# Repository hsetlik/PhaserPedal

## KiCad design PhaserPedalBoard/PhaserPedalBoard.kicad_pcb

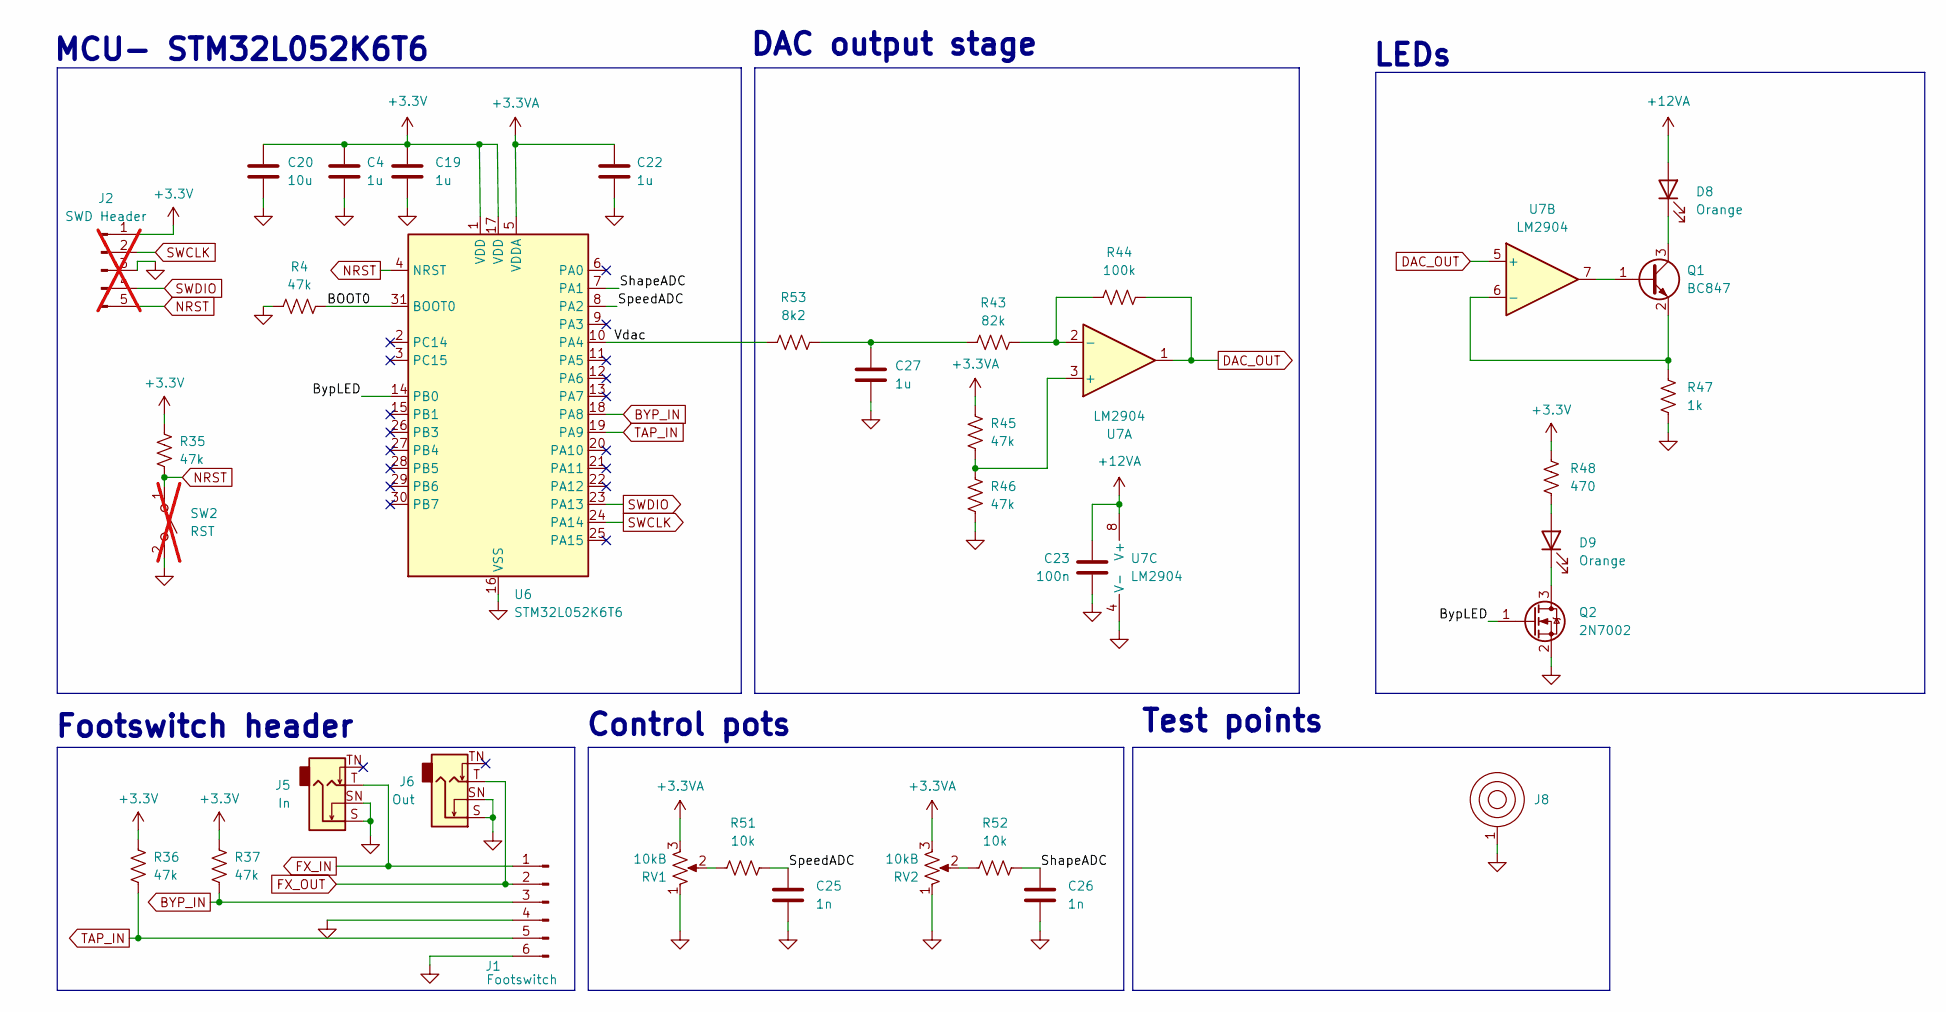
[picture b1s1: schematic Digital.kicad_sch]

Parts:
C4, C19, C22, C27: 1u; C_0805_2012Metric
C20: 10u; C_0805_2012Metric
C23: 100n; C_0805_2012Metric
C25, C26: 1n; C_0805_2012Metric
D8, D9: Orange; LED_D3.0mm; MPN LTL-4291N
J1: Footswitch; PinHeader_1x06_P2.54mm_Vertical
J2: SWD Header; PinHeader_1x05_P2.54mm_Vertical; not fitted
J5: In; Jack_6.35mm_Tayda_PJ664C_Mono_Horizontal; MPN PJ-644C MONO
J6: Out; Jack_6.35mm_Tayda_PJ664C_Mono_Horizontal; MPN PJ-644C MONO
J8: BatteryContact_Keystone_243
Q1: BC847; SOT-23
Q2: 2N7002; SOT-23; MPN 2N7002NXAKR
R4, R45, R46: 47k; R_0805_2012Metric
R35, R36, R37: 47k; R_0805_2012Metric; MPN RK73B2ATTE473J
R43: 82k; R_0805_2012Metric
R44: 100k; R_0805_2012Metric
R47: 1k; R_0805_2012Metric
R48: 470; R_0805_2012Metric; MPN RC0805JR-10470RL
R51, R52: 10k; R_0805_2012Metric
R53: 8k2; R_0805_2012Metric
RV1, RV2: 10kB; Potentiometer_Alpha_RV16AF_42_Single_Long; MPN RV9022NO-PA30B7.0-B10K-000-W3.0
SW2: RST; SW_SPST_B3U-1000P; not fitted
U6: STM32L052K6T6; LQFP-32_7x7mm_P0.8mm
U7: LM2904; SOIC-8_3.9x4.9mm_P1.27mm

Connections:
+3.3V: C4.1, C19.1, C20.1, J2.1, R35.1, R36.1, R37.1, R48.1, U6.1 (VDD), U6.17 (VDD); also elsewhere on the board
+3.3VA: C22.1, R45.2, RV1.3, RV2.3, U6.5 (VDDA); also elsewhere on the board
+12VA: C23.1, D8.2 (A), U7.8 (V+); also elsewhere on the board
/Digital/BOOT0: R4.2, U6.31 (BOOT0)
/Digital/BypLED: Q2.1 (G), U6.14 (PB0)
/Digital/ShapeADC: C26.1, R52.2, U6.7 (PA1)
/Digital/SpeedADC: C25.1, R51.2, U6.8 (PA2)
/Digital/Vdac: R53.1, U6.10 (PA4)
BYP_IN: J1.3, R37.2, U6.18 (PA8)
DAC_OUT: R44.2, U7.1, U7.5 (+); also elsewhere on the board
FX_IN: J1.1, J5.T; also elsewhere on the board
FX_OUT: J1.2, J6.T; also elsewhere on the board
GND: C4.2, C19.2, C20.2, C22.2, C23.2, C25.2, C26.2, C27.2, J1.4, J1.6, J2.3, J5.S, J5.SN, J6.S, J6.SN, J8.1, Q2.2 (S), R4.1, R46.1, R47.1, RV1.1, RV2.1, SW2.2 (B), U6.16 (VSS), U6.32 (VSS), U7.4 (V-); also elsewhere on the board
NRST: J2.5, R35.2, SW2.1 (A), U6.4 (NRST)
unnamed: C27.1, R43.1, R53.2
unnamed: D8.1 (K), Q1.3 (C)
unnamed: D9.2 (A), R48.2
unnamed: D9.1 (K), Q2.3 (D)
unnamed: Q1.1 (B), U7.7
unnamed: Q1.2 (E), R47.2, U7.6 (-)
unnamed: R51.1, RV1.2
unnamed: R52.1, RV2.2
unnamed: R45.1, R46.2, U7.3 (+)
unnamed: R43.2, R44.1, U7.2 (-)
SWCLK: J2.2, U6.24 (PA14)
SWDIO: J2.4, U6.23 (PA13)
TAP_IN: J1.5, R36.2, U6.19 (PA9)

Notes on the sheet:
Test points
MCU- STM32L052K6T6
LEDs
Footswitch header
Control pots
DAC output stage

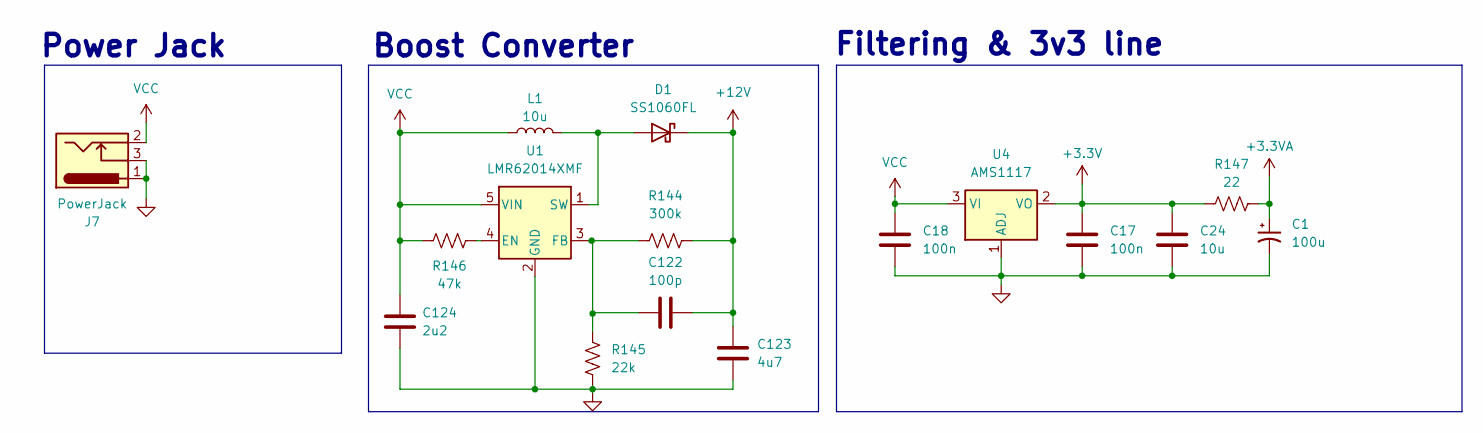
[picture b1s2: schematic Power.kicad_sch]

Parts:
C1: 100u; CP_Radial_D6.3mm_P2.50mm
C17, C18: 100n; C_0805_2012Metric; MPN KGF21BR71H104KT
C24: 10u; C_0805_2012Metric; MPN KGM21AR50J106KU
C122: 100p; C_0805_2012Metric
C123: 4u7; C_0805_2012Metric
C124: 2u2; C_0805_2012Metric
D1: SS1060FL; D_SOD-123F
J7: PowerJack; BarrelJack_Horizontal; MPN NEB 21 R-C
L1: 10u; L_SigTransformer_SLPPI04_15
R144: 300k; R_0805_2012Metric
R145: 22k; R_0805_2012Metric
R146: 47k; R_0805_2012Metric
R147: 22; R_0805_2012Metric
U1: LMR62014XMF; SOT-23-5
U4: AMS1117; SOT-223-3_TabPin2; MPN LD1117S33CTR

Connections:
+3.3V: C17.2, C24.2, R147.2, U4.2 (VO); also elsewhere on the board
+3.3VA: C1.1, R147.1; also elsewhere on the board
+12V: C122.2, C123.1, D1.1 (K), R144.2; also elsewhere on the board
GND: C1.2, C17.1, C18.1, C24.1, C123.2, C124.2, J7.1, J7.3, R145.1, U1.2 (GND), U4.1 (ADJ); also elsewhere on the board
unnamed: D1.2 (A), L1.2, U1.1 (SW)
unnamed: R146.2, U1.4 (EN)
unnamed: C122.1, R144.1, R145.2, U1.3 (FB)
VCC: C18.2, C124.1, J7.2, L1.1, R146.1, U1.5 (VIN), U4.3 (VI)

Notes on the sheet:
Power Jack
Filtering & 3v3 line
Boost Converter

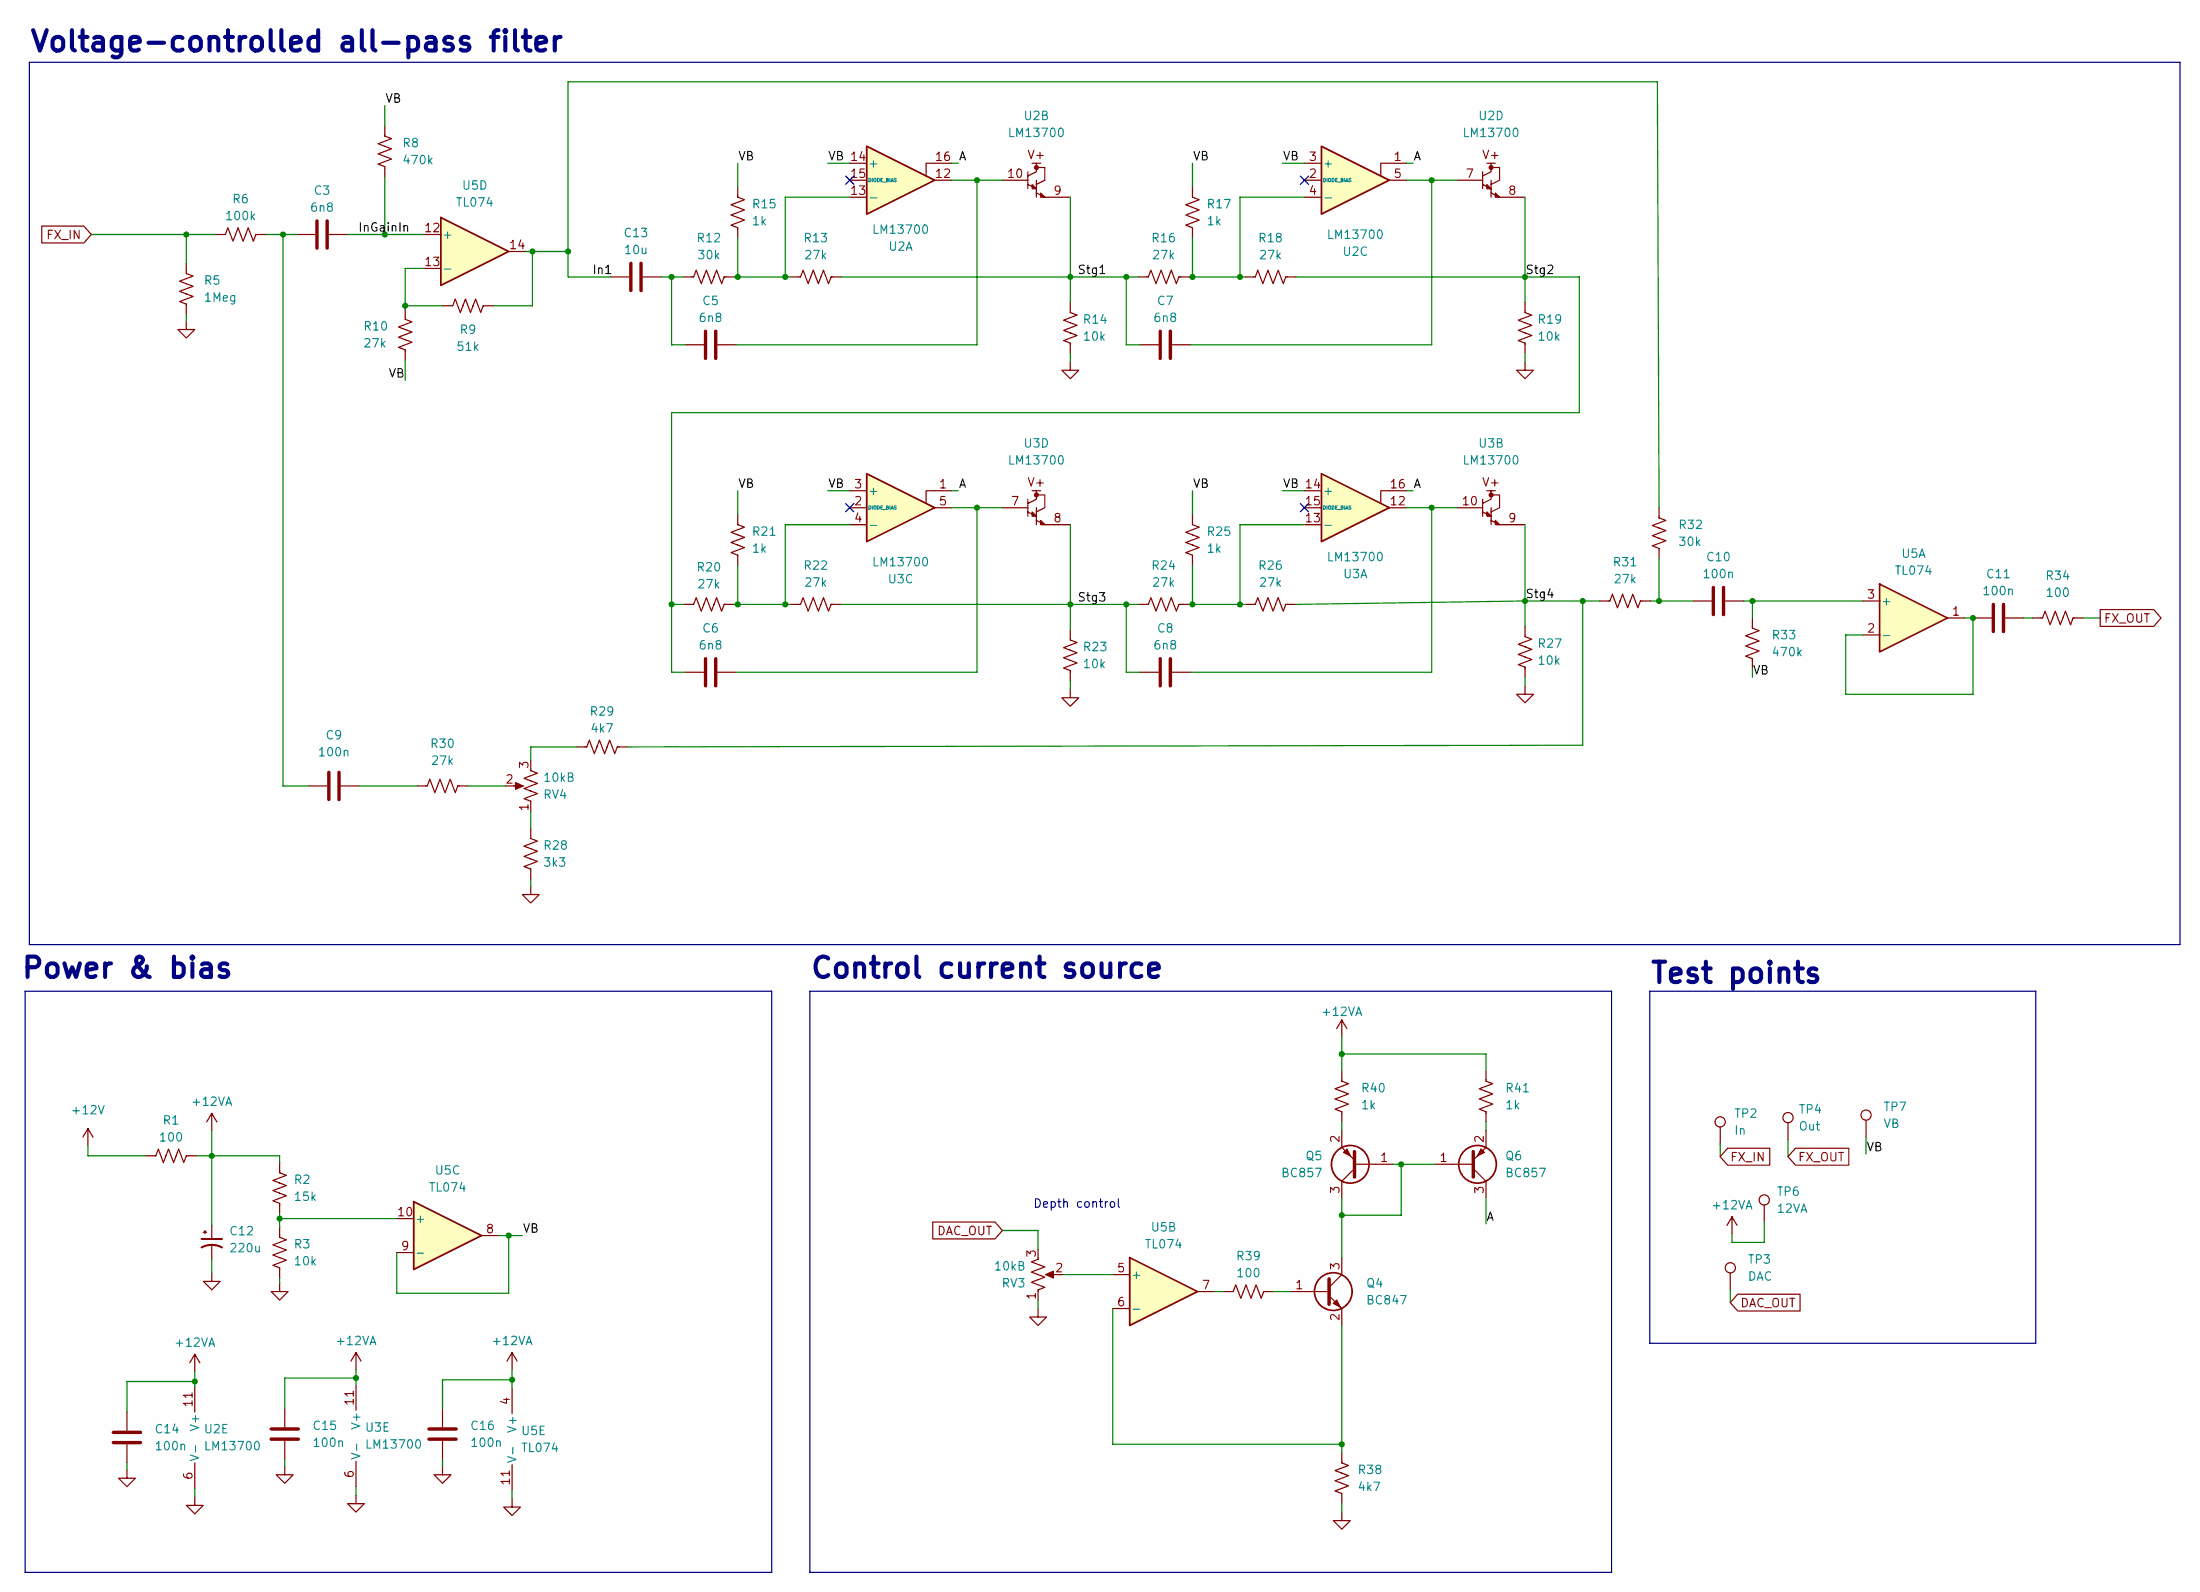
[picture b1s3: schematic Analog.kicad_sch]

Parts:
C3, C5, C6, C7, C8: 6n8; C_0805_2012Metric
C9, C10, C11, C14, C15, C16: 100n; C_0805_2012Metric
C12: 220u; CP_Radial_D7.5mm_P2.50mm
C13: 10u; C_0805_2012Metric
Q4: BC847; SOT-23
Q5, Q6: BC857; SOT-23
R1, R34, R39: 100; R_0805_2012Metric
R2: 15k; R_0805_2012Metric
R3, R14, R19, R23, R27: 10k; R_0805_2012Metric
R5: 1Meg; R_0805_2012Metric
R6: 100k; R_0805_2012Metric
R8, R33: 470k; R_0805_2012Metric
R9: 51k; R_0805_2012Metric
R10, R13, R16, R18, R20, R22, R24, R26, R30, R31: 27k; R_0805_2012Metric
R12, R32: 30k; R_0805_2012Metric
R15, R17, R21, R25, R40, R41: 1k; R_0805_2012Metric
R28: 3k3; R_0805_2012Metric
R29, R38: 4k7; R_0805_2012Metric
RV3, RV4: 10kB; Potentiometer_Alpha_RV16AF_42_Single_Long; MPN RV9022NO-PA30B7.0-B10K-000-W3.0
TP2: In; TestPoint_THTPad_D2.0mm_Drill1.0mm_VAL
TP3: DAC; TestPoint_THTPad_D2.0mm_Drill1.0mm_VAL
TP4: Out; TestPoint_THTPad_D2.0mm_Drill1.0mm_VAL
TP6: 12VA; TestPoint_THTPad_D2.0mm_Drill1.0mm_VAL
TP7: VB; TestPoint_THTPad_D2.0mm_Drill1.0mm_VAL
U2, U3: LM13700; SOIC-16_3.9x9.9mm_P1.27mm
U5: TL074; SOIC-14_3.9x8.7mm_P1.27mm

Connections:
+12V: R1.1; also elsewhere on the board
+12VA: C12.1, C14.2, C15.2, C16.2, R1.2, R2.2, R40.2, R41.2, TP6.1 (1_1), U2.11 (V+), U3.11 (V+), U5.4 (V+); also elsewhere on the board
/Analog/A: Q6.3 (C), U2.1, U2.16, U3.1, U3.16
/Analog/In1: C13.1, R9.1, R32.1, U5.14
/Analog/InGainIn: C3.2, R8.1, U5.12 (+)
/Analog/Stg1: C7.1, R13.1, R14.1, R16.2, U2.9
/Analog/Stg2: C6.1, R18.1, R19.1, R20.2, U2.8
/Analog/Stg3: C8.1, R22.1, R23.1, R24.2, U3.8
/Analog/Stg4: R26.1, R27.1, R29.2, R31.2, U3.9
/Analog/VB: R8.2, R10.2, R15.1, R17.1, R21.1, R25.1, R33.2, TP7.1 (1_1), U2.3 (+), U2.14 (+), U3.3 (+), U3.14 (+), U5.8, U5.9 (-)
DAC_OUT: RV3.3, TP3.1 (1_1); also elsewhere on the board
FX_IN: R5.2, R6.1, TP2.1 (1_1); also elsewhere on the board
FX_OUT: R34.1, TP4.1 (1_1); also elsewhere on the board
GND: C12.2, C14.1, C15.1, C16.1, R3.1, R5.1, R14.2, R19.2, R23.2, R27.2, R28.1, R38.1, RV3.1, U2.6 (V-), U3.6 (V-), U5.11 (V-); also elsewhere on the board
unnamed: C3.1, C9.1, R6.2
unnamed: C5.2, U2.10, U2.12
unnamed: C6.2, U3.5, U3.7
unnamed: C7.2, U2.5, U2.7
unnamed: C8.2, U3.10, U3.12
unnamed: C9.2, R30.1
unnamed: C10.1, R31.1, R32.2
unnamed: C11.2, R34.2
unnamed: C5.1, C13.2, R12.2
unnamed: Q4.1 (B), R39.2
unnamed: Q4.3 (C), Q5.1 (B), Q5.3 (C), Q6.1 (B)
unnamed: Q4.2 (E), R38.2, U5.6 (-)
unnamed: Q5.2 (E), R40.1
unnamed: Q6.2 (E), R41.1
unnamed: R28.2, RV4.1
unnamed: R29.1, RV4.3
unnamed: R30.2, RV4.2
unnamed: R39.1, U5.7
unnamed: R12.1, R13.2, R15.2, U2.13 (-)
unnamed: R16.1, R17.2, R18.2, U2.4 (-)
unnamed: R24.1, R25.2, R26.2, U3.13 (-)
unnamed: R20.1, R21.2, R22.2, U3.4 (-)
unnamed: C10.2, R33.1, U5.3 (+)
unnamed: C11.1, U5.1, U5.2 (-)
unnamed: RV3.2, U5.5 (+)
unnamed: R2.1, R3.2, U5.10 (+)
unnamed: R9.2, R10.1, U5.13 (-)

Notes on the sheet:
Control current source
Test points
Voltage-controlled all-pass filter
Depth control
Power & bias

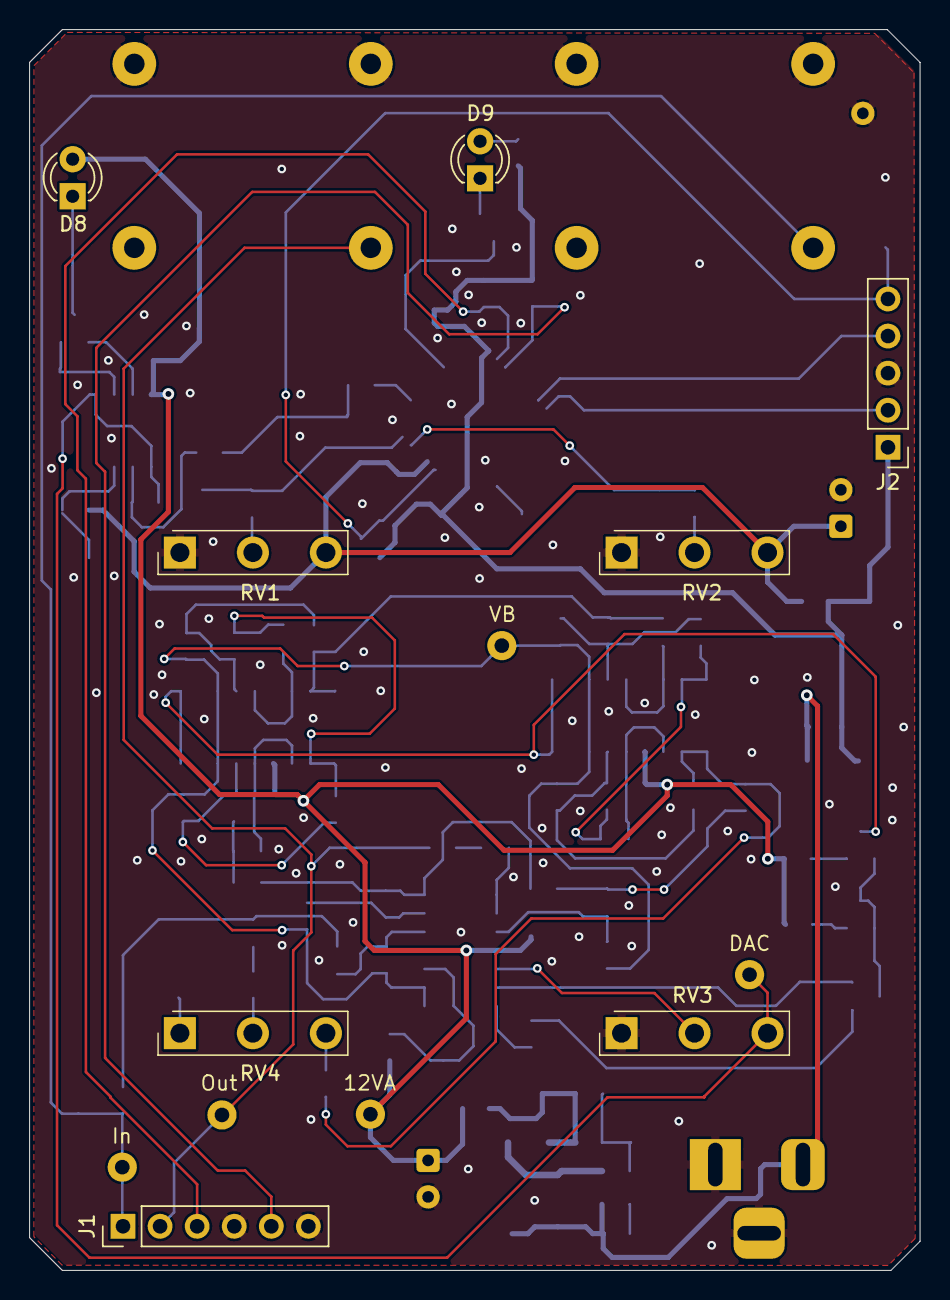
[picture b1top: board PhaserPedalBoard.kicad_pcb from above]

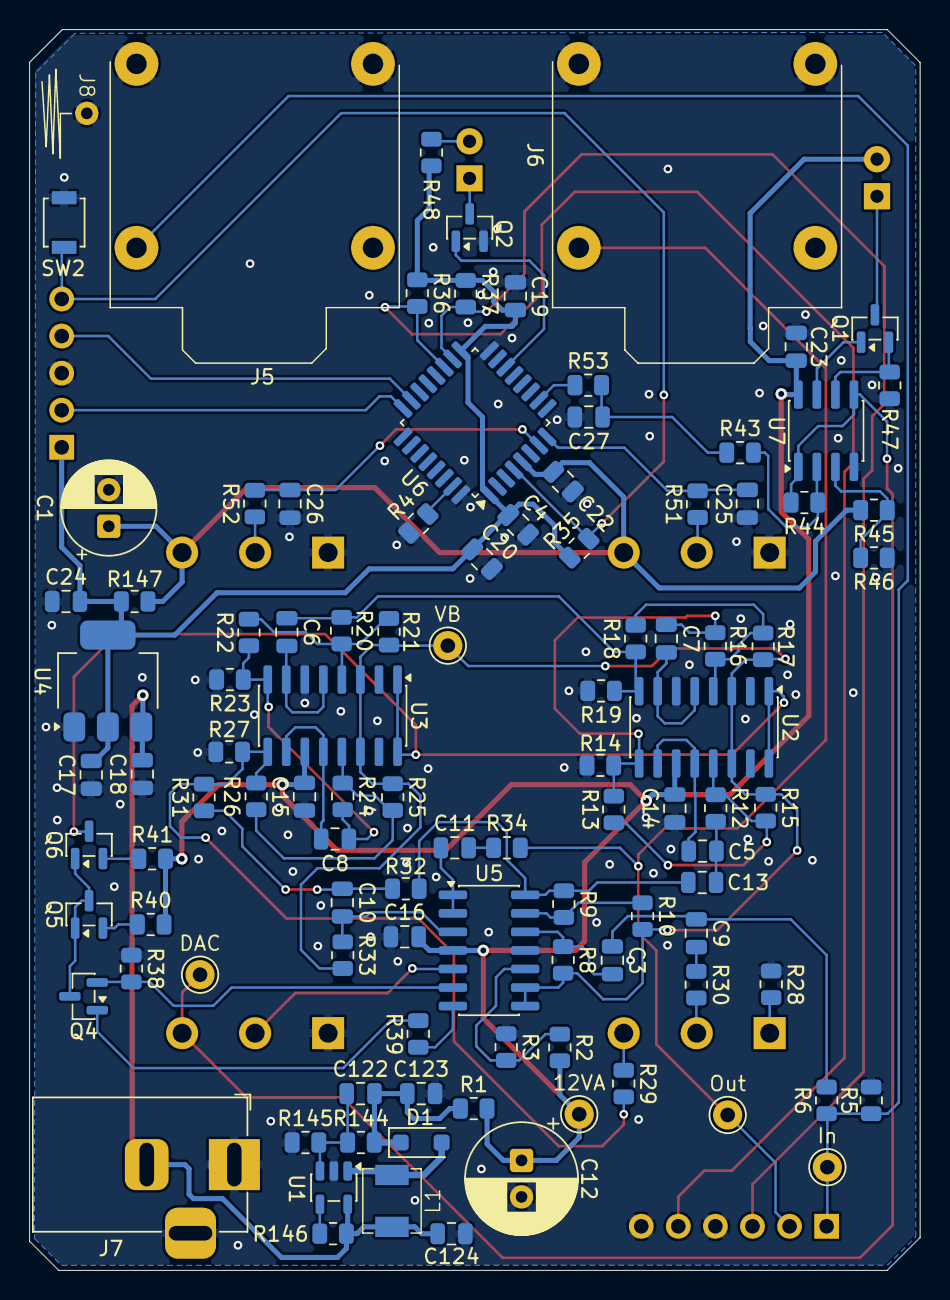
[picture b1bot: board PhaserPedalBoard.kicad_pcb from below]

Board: 4 copper layers, 61.0 x 85.0 mm, 112 parts (104 on the bottom side), 67 nets.

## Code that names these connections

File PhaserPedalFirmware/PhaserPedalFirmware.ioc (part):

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Mcu.Name=STM32L052K(6-8)Tx
Mcu.Package=LQFP32
Mcu.UserName=STM32L052K6Tx
PA1.GPIOParameters=GPIO_Label
PA1.GPIO_Label=SPEED_IN
PA1.Mode=IN1
PA1.Signal=ADC_IN1
PA13.Mode=Serial_Wire
PA13.Signal=SYS_SWDIO
PA14.Mode=Serial_Wire
PA14.Signal=SYS_SWCLK
PA2.GPIOParameters=GPIO_Label
PA2.GPIO_Label=SHAPE_IN
PA2.Mode=IN2
PA2.Signal=ADC_IN2
PA4.Signal=COMP_DAC1_group
PA8.GPIOParameters=GPIO_Label
PA8.GPIO_Label=BYPASS_IN
PA8.Signal=GPIO_Input
PA9.GPIOParameters=GPIO_Label
PA9.GPIO_Label=TAP_IN
PA9.Signal=GPIO_Input
PB0.GPIOParameters=GPIO_Label
PB0.GPIO_Label=BYP_LED
PB0.Signal=GPIO_Output
RCC.SYSCLKFreq_VALUE=24000000
RCC.SYSCLKSource=RCC_SYSCLKSOURCE_PLLCLK
board=custom
